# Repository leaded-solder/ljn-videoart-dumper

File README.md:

# LJN Video Art cartridge dumper
In 1987, toy company LJN made a home game console called the "[Video Art](https://en.wikipedia.org/wiki/LJN_Video_Art)." It has a handful of games that come on cartridges and is 6805-based.

This repo contains the source for a hardware/software combination to dump these cartridges to ROM files, which can be used in a hypothetical future emulator or clone device.

This device was developed as part of [a Leaded Solder blog](https://www.leadedsolder.com) entry. It cost money and time to develop; if you want to support things like this in the future, please contribute to the Patreon.

## Dumped Games
So far, only one game has been dumped by this device:
 - Disney Story Book

The remaining eight games of the Video Art system have been dumped by others:
 - Video Art Activity Cartridge `ljn_act-1`
 - A Trip to the Zoo `tripzoo`
 - Disney Colouring Book `disneycb`
 - Looney Tunes `looney`
 - Marvel Super-Heroes `marvel`
 - My Dream Day `dreamday`
 - My Favorite Doll `favdoll`
 - On the Move `onmove`

If you have a Video Art cartridge that is not listed here, please get in touch.

## Hardware
### Requirements
You will need:
 - An Arduino Uno or compatible. I used the "Elegoo Uno R3" from Amazon for development and testing;
 - A USB cable;
 - 2x DIP 74HCT595 (74HC595 is probably fine);
 - 1x DIP 74HCT165 (74HC165 is probably fine);
 - The cartridge slot for the LJN cartridge, I used a [TE AMP 5530843-3](https://www.te.com/usa-en/product-5530843-3.html);
 - A length of component leg (e.g. leftover resistor) or some wire;
 - Arduino shield stacking headers (I got mine off Amazon)

### Assembly Instructions
Assembly is a bit tricky, so go shortest to tallest component as you are populating the board. The stacking connectors should go last.

The cartridge connector should be tilted back slightly to make sure there is clearance with the stacking connectors.

Stick a wire or a bent resistor leg through the "0Ω" resistor footprint on the board.

There is no need to populate the two test points TP1 or TP2; these are meant for a beaded test hook, in order to debug the board using a logic probe.

It is challenging to make the stacking connectors go in straight; if you have a better way, please let me know. I used sticky tack/poster putty and bent the pins to mate with the Uno base board.

## Software
### Build instructions
 1. Install Arduino IDE. I developed this with version 2.2.1, but I assume any Arduino editor should work for this purpose.
 2. Open the `.ino` file.
 3. Connect your Arduino Uno (or compatible) to the USB port and upload the firmware to the board. This might require some configuration; check your board vendor for more details.
 4. Insert the cartridge. The label side of the cartridge must face outwards, towards the text on the PCB that says "label side this way."

### Usage instructions
For now, there is no software client for this dumper. Instead, you'll want to use the Serial Monitor from the Arduino IDE.

When the Uno starts up, it should display a message like this:

```
LJN VideoArt ROM Dumper
OE is on pin 10
```

Type `dump` into the text input, press return, and wait for the dump to complete. The monitor should slowly fill with hexadecimal values from the ROM, followed by the message `done.`

Open the `interpreter.py` Python script in your favourite text editor.

Copy and paste the hex values from the Arduino Serial Monitor output into the string `DUMP_STRING`. Make sure none of the old string is there, and make sure it makes a valid Python string (i.e. that it is surrounded by single quotes and is all one line.)

Run the `interpreter.py` Python script. It should generate a file called `rom.bin` that is exactly 16,384 bytes long.

If you know that your ROM is longer than 16,384 bytes, this board may not work for you. Please contact me immediately and we'll work something out.

### Other Commands
Not many commands are supported; this list is here for mostly diagnostic purposes.

| Command | Does what? |
|---------|------------|
| `dump`  | Dumps a 16K ROM |
| `info`  | Version identification for the firmware. |
| `oelo`  | Pulls the output-enable line of the cartridge LOW (enabled) |
| `oehi`  | Pulls the output-enable line of the cartridge HIGH (disabled) |

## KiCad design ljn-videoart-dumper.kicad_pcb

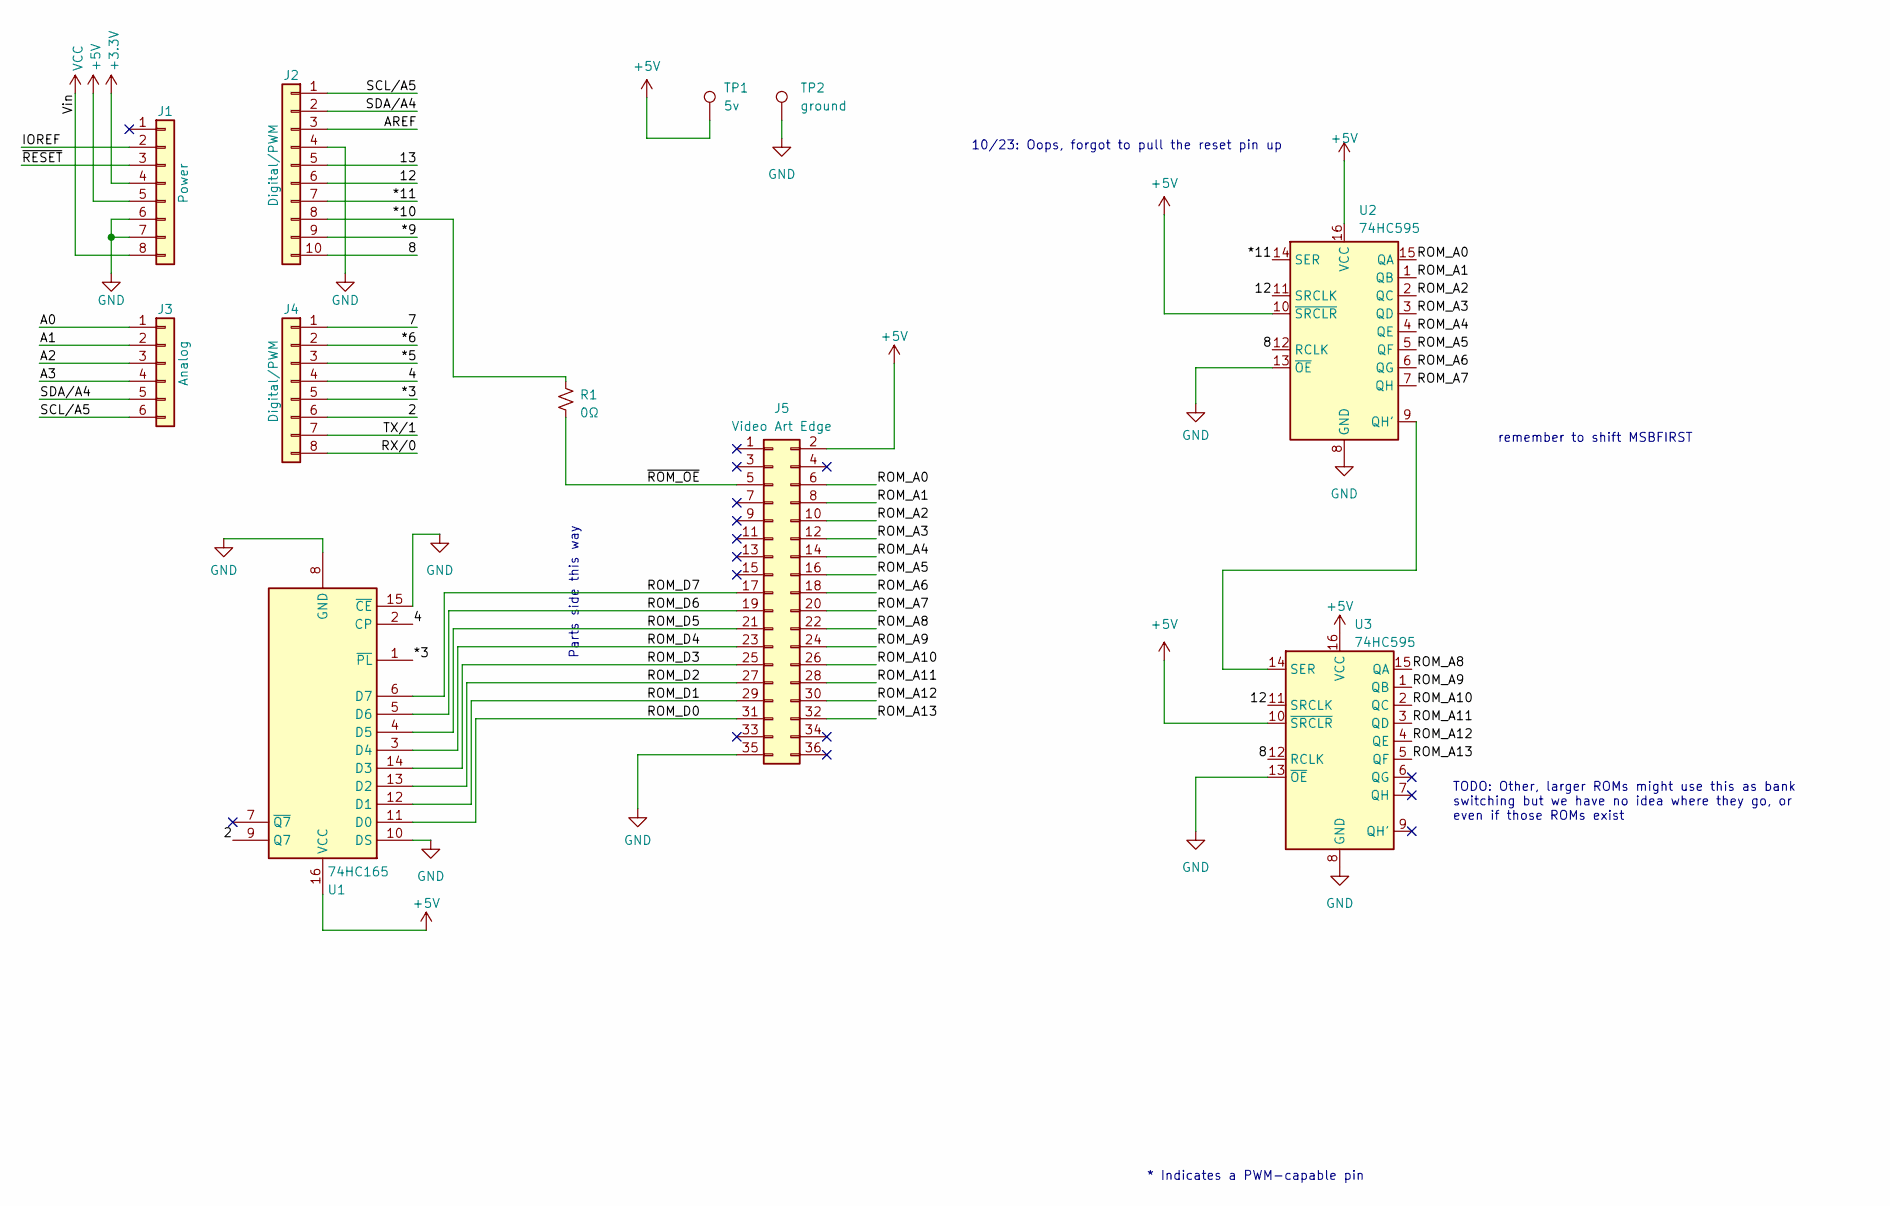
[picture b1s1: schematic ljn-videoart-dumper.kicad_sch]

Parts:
J1: Power; PinSocket_1x08_P2.54mm_Vertical
J2: Digital/PWM; PinSocket_1x10_P2.54mm_Vertical
J3: Analog; PinSocket_1x06_P2.54mm_Vertical
J4: Digital/PWM; PinSocket_1x08_P2.54mm_Vertical
J5: Video Art Edge; CONN_5530843-3_TYC
R1: 0Ω; R_Axial_DIN0207_L6.3mm_D2.5mm_P10.16mm_Horizontal
TP1: 5v; TestPoint_Loop_D2.54mm_Drill1.5mm_Beaded
TP2: ground; TestPoint_Loop_D2.54mm_Drill1.5mm_Beaded
U1: 74HC165; DIP-16_W7.62mm_Socket_LongPads
U2, U3: 74HC595; DIP-16_W7.62mm_Socket_LongPads

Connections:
+3V3: J1.4
+5V: J1.5, J5.2, TP1.1, U1.16 (VCC), U2.10 (~SRCLR), U2.16 (VCC), U3.10 (~SRCLR), U3.16 (VCC)
/2: J4.6, U1.9 (Q7)
/4: J4.4, U1.2 (CP)
/7: J4.1
/8: J2.10, U2.12 (RCLK), U3.12 (RCLK)
/12: J2.6, U2.11 (SRCLK), U3.11 (SRCLK)
/13: J2.5
/*3: J4.5, U1.1 (~PL)
/*5: J4.3
/*6: J4.2
/*9: J2.9
/*10: J2.8, R1.1
/*11: J2.7, U2.14 (SER)
/A0: J3.1
/A1: J3.2
/A2: J3.3
/A3: J3.4
/AREF: J2.3
/IOREF: J1.2
/ROM_A0: J5.6, U2.15 (QA)
/ROM_A1: J5.8, U2.1 (QB)
/ROM_A2: J5.10, U2.2 (QC)
/ROM_A3: J5.12, U2.3 (QD)
/ROM_A4: J5.14, U2.4 (QE)
/ROM_A5: J5.16, U2.5 (QF)
/ROM_A6: J5.18, U2.6 (QG)
/ROM_A7: J5.20, U2.7 (QH)
/ROM_A8: J5.22, U3.15 (QA)
/ROM_A9: J5.24, U3.1 (QB)
/ROM_A10: J5.26, U3.2 (QC)
/ROM_A11: J5.28, U3.3 (QD)
/ROM_A12: J5.30, U3.4 (QE)
/ROM_A13: J5.32, U3.5 (QF)
/ROM_D0: J5.31, U1.11 (D0)
/ROM_D1: J5.29, U1.12 (D1)
/ROM_D2: J5.27, U1.13 (D2)
/ROM_D3: J5.25, U1.14 (D3)
/ROM_D4: J5.23, U1.3 (D4)
/ROM_D5: J5.21, U1.4 (D5)
/ROM_D6: J5.19, U1.5 (D6)
/ROM_D7: J5.17, U1.6 (D7)
/RX/0: J4.8
/SCL/A5: J2.1, J3.6
/SDA/A4: J2.2, J3.5
/TX/1: J4.7
/~RESET: J1.3
/~ROM_OE: J5.5, R1.2
GND: J1.6, J1.7, J2.4, J5.35, TP2.1, U1.8 (GND), U1.10 (DS), U1.15 (~CE), U2.8 (GND), U2.13 (~OE), U3.8 (GND), U3.13 (~OE)
unnamed: U2.9 (QH'), U3.14 (SER)
VCC: J1.8

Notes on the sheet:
remember to shift MSBFIRST
TODO: Other, larger ROMs might use this as bank switching but we have no idea where they go, or even if those ROMs exist
10/23: Oops, forgot to pull the reset pin up
* Indicates a PWM-capable pin
Parts side this way

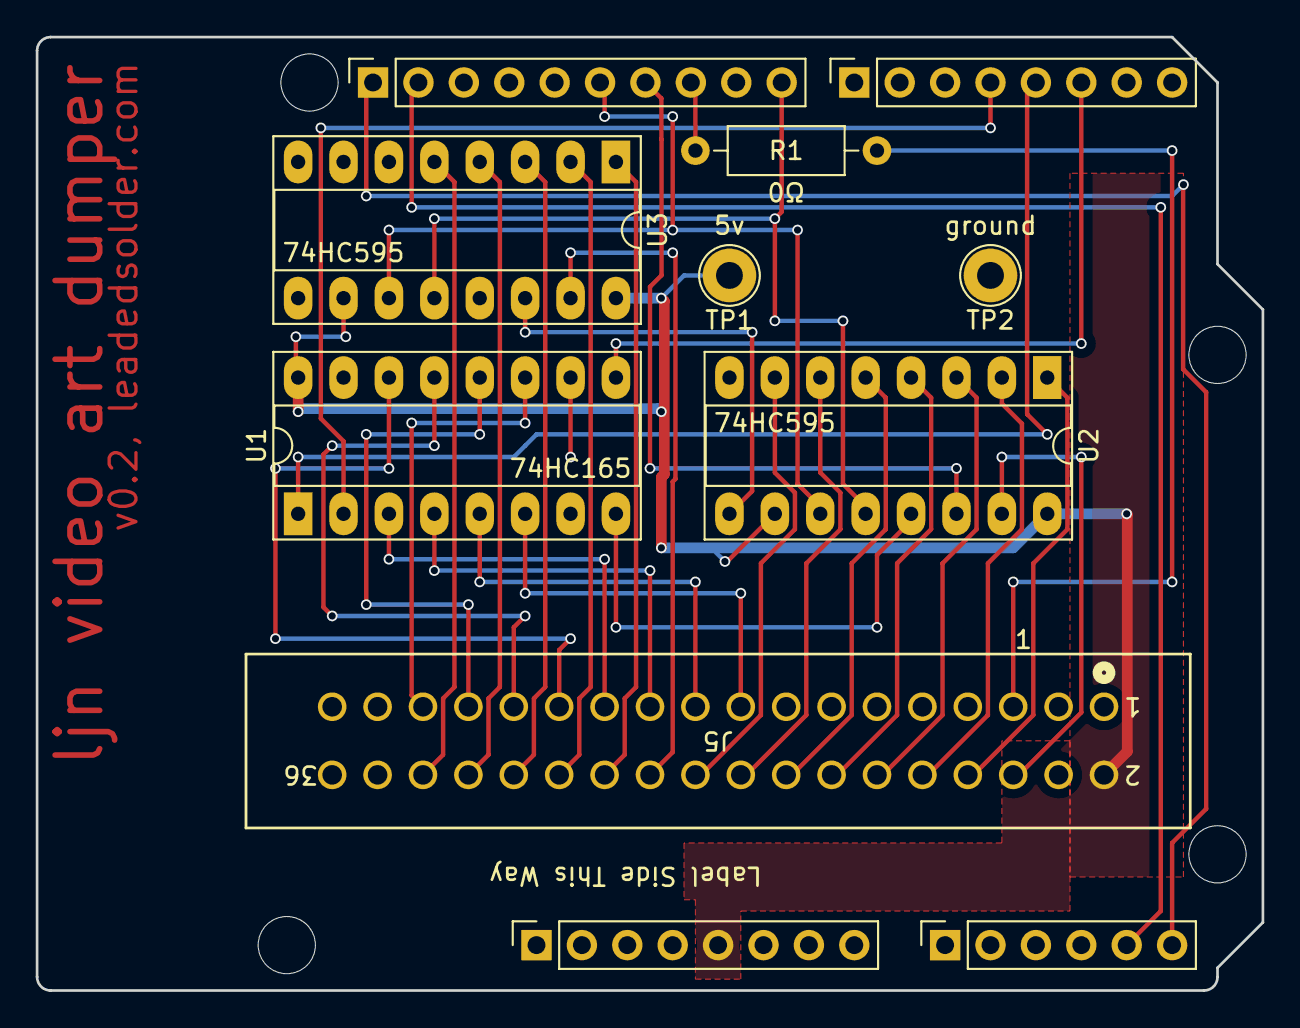
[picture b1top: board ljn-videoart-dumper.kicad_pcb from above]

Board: 2 copper layers, 68.6 x 53.3 mm, 15 parts (0 on the bottom side), 35 nets.

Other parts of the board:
MH1, MH2, MH3, MH4: MountingHole_3.2mm

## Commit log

2023-05-31 Pinout of cartridge edge
2023-06-02 Add connector
2023-06-02 Fix pin numbering before it gets embarrassing
2023-06-02 Rearrangement
2023-06-02 595s
2023-06-02 Final re-route
2023-06-02 V1 released to JLCPCB
2023-06-02 not sure why plot didn't include edge.cuts or silk, but fixed now
2023-06-17 Untested Arduino firmware
2023-06-20 Dumping not working
2023-06-20 Nothing I'm doing with address pins seems to matter?
2023-07-05 Move everything away from the USB-port
2023-07-05 Fix cart slot labels
2023-07-05 0-ohm label
2023-10-10 Fix errors, add 5v/gnd test points
2023-10-10 5v/gnd markings
2023-10-10 Messing with labels
2023-10-11 Short MR to 5V
2023-10-11 Got a plausible dump out, now converted to ROM.bin
2023-10-11 Confirmed MSBFIRST is correct
2023-10-11 README first draft
2023-10-11 Blog link
2023-10-11 Command list
2023-10-11 Cartridge info
2023-10-11 please let me know if you have carts to dump
2023-10-25 Improve ignore
2023-11-08 Add remaining eight games under 'dumped'
